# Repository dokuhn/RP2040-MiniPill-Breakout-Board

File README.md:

# RP2040-MiniPill-Breakout-Board

[![CC BY-NC-SA 4.0][cc-by-nc-sa-shield]][cc-by-nc-sa]

## Development Renderings

### Schematic

### Simulation

|   |   |
| :------: | :------: |
| LTspice Schematic | Simulation |

## Concept Renderings

|   |   |
| :------: | :------: |
| Top | Animation |

## License 

This work is licensed under a
[Creative Commons Attribution-NonCommercial-ShareAlike 4.0 International License][cc-by-nc-sa].

[![CC BY-NC-SA 4.0][cc-by-nc-sa-image]][cc-by-nc-sa]

[cc-by-nc-sa]: http://creativecommons.org/licenses/by-nc-sa/4.0/
[cc-by-nc-sa-image]: https://licensebuttons.net/l/by-nc-sa/4.0/88x31.png
[cc-by-nc-sa-shield]: https://img.shields.io/badge/License-CC%20BY--NC--SA%204.0-lightgrey.svg

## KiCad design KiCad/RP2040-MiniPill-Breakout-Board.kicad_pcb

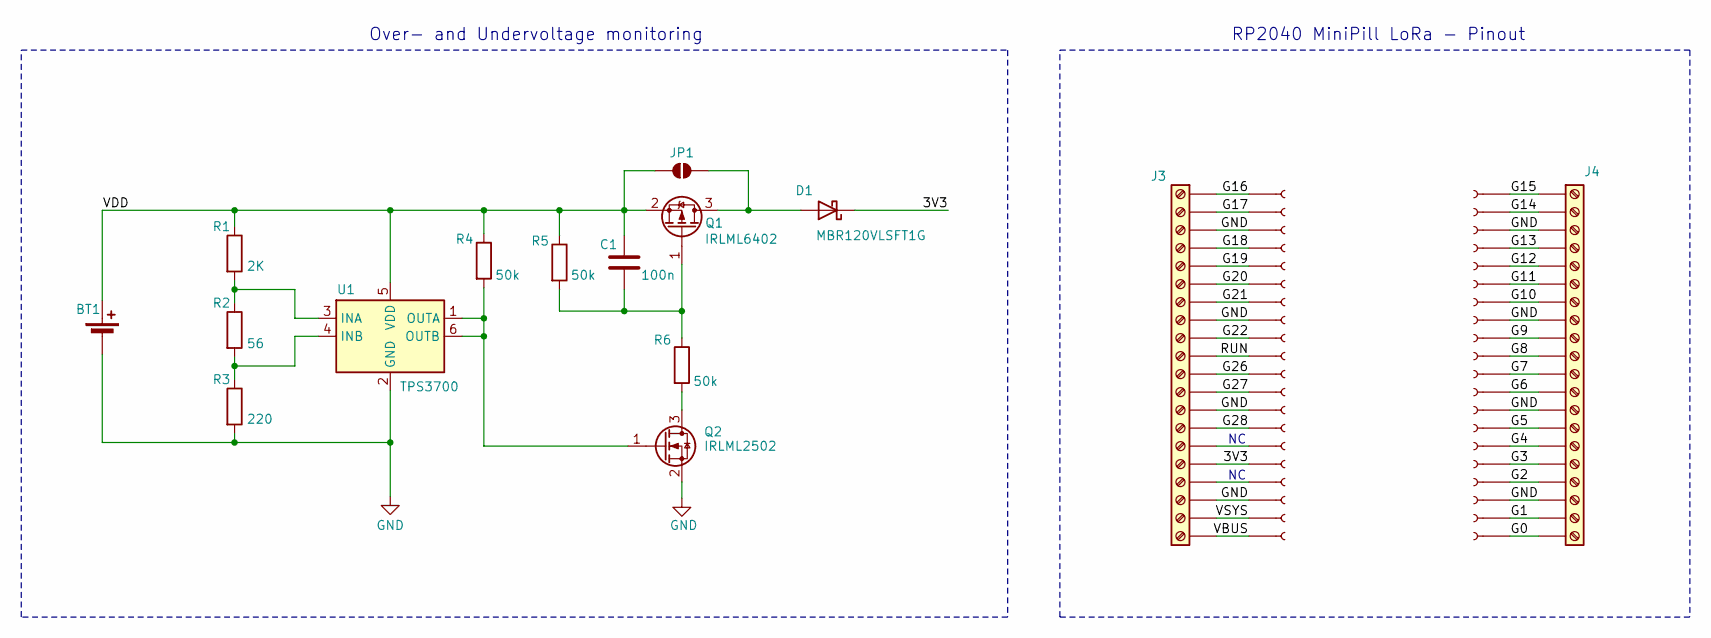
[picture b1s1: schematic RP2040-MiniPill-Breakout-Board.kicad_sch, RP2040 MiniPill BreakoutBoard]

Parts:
BT1: Battery_Cell; BatteryHolder_Keystone_2460_1xAA; LCSC C5290181
C1: 100n; C_0603_1608Metric_Pad1.08x0.95mm_HandSolder; LCSC C14663
D1: MBR120VLSFT1G; D_SOD-123F; LCSC C223608
J1, J2: Conn_01x20_Socket; PinSocket_1x20_P2.54mm_Vertical
J3, J4: Screw_Terminal_01x20; TerminalBlock_Xinya_XY308-2.54-20P_1x20_P2.54mm_Horizontal; LCSC C915914 (4x)
JP1: SolderJumper_2_Open; SolderJumper-2_P1.3mm_Open_TrianglePad1.0x1.5mm
Q1: IRLML6402; SOT-23; LCSC C2593
Q2: IRLML2502; SOT-23; LCSC C2589
R1: 2K; R_0603_1608Metric_Pad0.98x0.95mm_HandSolder; LCSC C22975
R2: 56; R_0603_1608Metric_Pad0.98x0.95mm_HandSolder; LCSC C22775
R3: 220; R_0603_1608Metric_Pad0.98x0.95mm_HandSolder; LCSC C22962
R4, R5, R6: 50k; R_0603_1608Metric_Pad0.98x0.95mm_HandSolder; LCSC C861451
U1: TPS3700; SOT-23-6; LCSC C33002

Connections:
/3V3: D1.1 (K), J1.16, J3.16
/G0: J2.20, J4.20
/G1: J2.19, J4.19
/G2: J2.17, J4.17
/G3: J2.16, J4.16
/G4: J2.15, J4.15
/G5: J2.14, J4.14
/G6: J2.12, J4.12
/G7: J2.11, J4.11
/G8: J2.10, J4.10
/G9: J2.9, J4.9
/G10: J2.7, J4.7
/G11: J2.6, J4.6
/G12: J2.5, J4.5
/G13: J2.4, J4.4
/G14: J2.2, J4.2
/G15: J2.1, J4.1
/G16: J1.1, J3.1
/G17: J1.2, J3.2
/G18: J1.4, J3.4
/G19: J1.5, J3.5
/G20: J1.6, J3.6
/G21: J1.7, J3.7
/G22: J1.9, J3.9
/G26: J1.11, J3.11
/G27: J1.12, J3.12
/G28: J1.14, J3.14
/RUN: J1.10, J3.10
/VBUS: J1.20, J3.20
/VDD: BT1.1 (+), C1.1, JP1.1 (A), Q1.2 (S), R1.1, R4.1, R5.1, U1.5 (VDD); also elsewhere on the board
/VSYS: J1.19, J3.19
GND: BT1.2 (-), J1.3, J1.8, J1.13, J1.18, J2.3, J2.8, J2.13, J2.18, J3.3, J3.8, J3.13, J3.18, J4.3, J4.8, J4.13, J4.18, Q2.2 (S), R3.2, U1.2 (GND); also elsewhere on the board
unnamed: D1.2 (A), JP1.2 (B), Q1.3 (D)
unnamed: J1.15, J3.15
unnamed: J1.17, J3.17
unnamed: C1.2, Q1.1 (G), R5.2, R6.1
unnamed: Q2.3 (D), R6.2
unnamed: Q2.1 (G), R4.2, U1.1 (OUTA), U1.6 (OUTB)
unnamed: R1.2, R2.1, U1.3 (INA)
unnamed: R2.2, R3.1, U1.4 (INB)

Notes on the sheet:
Over- and Undervoltage monitoring
RP2040 MiniPill LoRa - Pinout

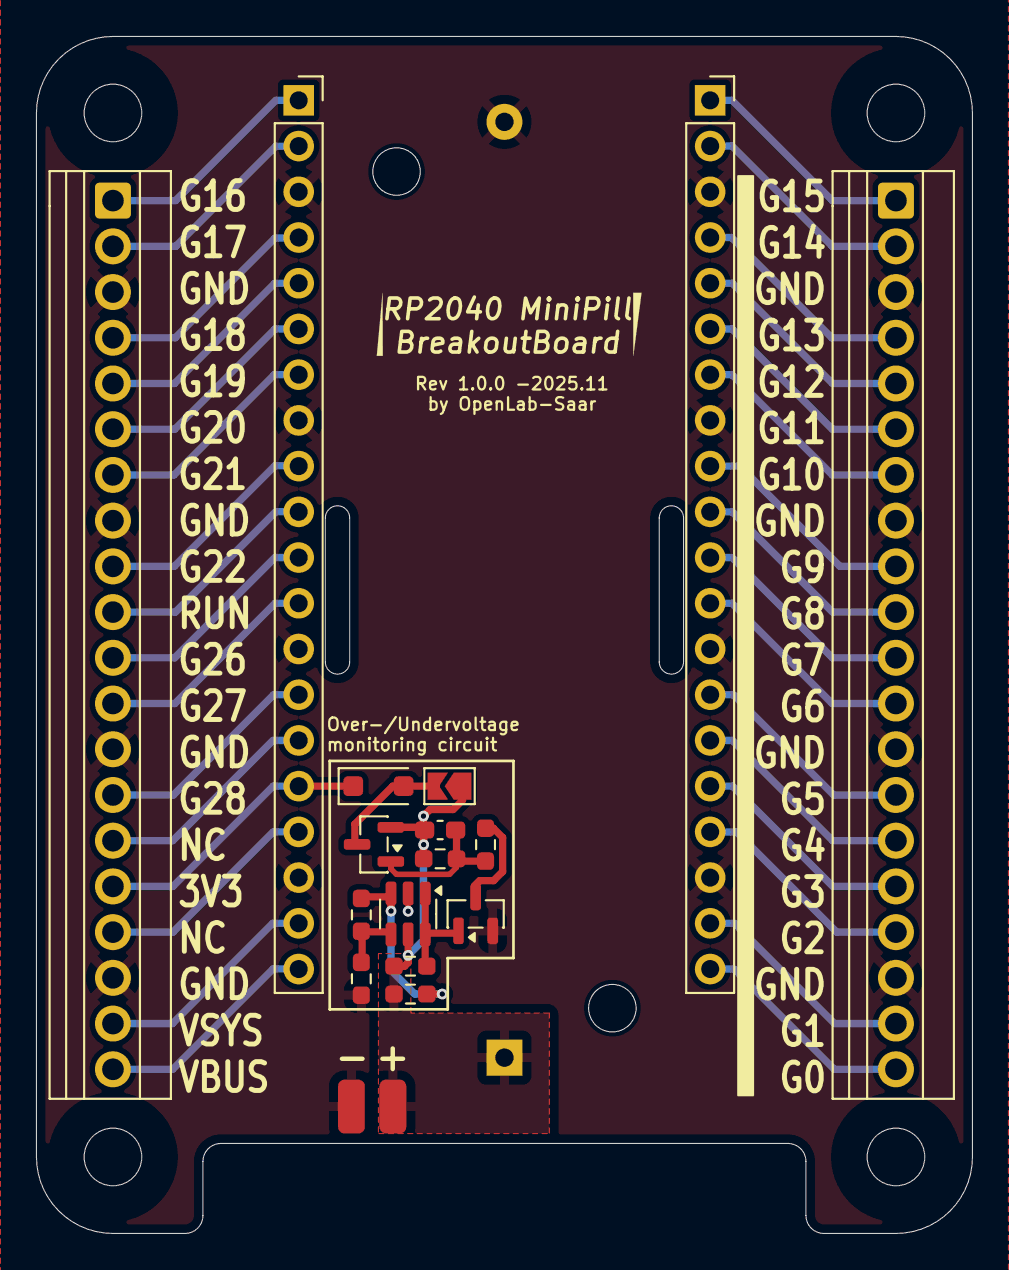
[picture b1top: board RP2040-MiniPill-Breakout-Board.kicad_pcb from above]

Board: 2 copper layers, 52.0 x 66.5 mm, 19 parts (1 on the bottom side), 40 nets.

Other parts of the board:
GND: SolderWirePad_1x01_SMD_1.5x3mm
VDD: SolderWirePad_1x01_SMD_1.5x3mm

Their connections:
/VDD: VDD.1; also elsewhere on the board
GND: GND.1; also elsewhere on the board

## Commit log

2025-06-10 adding Batteryholder
2025-07-01 Making some finetuning of 3dmodels. Adding aimation to README file.
2025-07-16 adding over and undervoltage monitoring
2025-10-01 adding Simulation
2025-11-03 adding diode and making first placement
2025-11-04 adding LCSC Parts
2025-11-05 making some finetuning and adding silkscreens, 3dvieports, etc.
2025-11-06 making some finetuning
2025-11-11 adding some LCSC parts and making some finetuning
2025-11-17 adding LCSC No for some parts
2025-11-18 adding custom Drawing Sheet and making some finetuning
2025-11-20 adding ibom
2025-11-20 making changes of the drawing sheet for pcb
2026-02-27 changing UV
